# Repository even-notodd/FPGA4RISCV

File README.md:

# FPGA4RISCV
This project is an attempt to build hardware (SOM and baseboard) capable of runnig Linux on RISCV MCU implemented in FPGA.
## This is work in progress, not finished project (!).
Overview: 

[Edit this diagram](https://app.diagrams.net/?url=https://raw.githubusercontent.com/even-notodd/FPGA4RISCV/DOCs/architecture.drawio)

# SOM
SOM is supposed to be designed in a format of a SO-DIMM card (Small Outline Dual Inline Memory Module) with standard 200 pin board edge connector.
SoM is based on Lattice FPGA chip LFE5UM5G-85F with dedicated DDR3 memory.

# Baseboard
Baseboard is supposed to be more or less generic baseboard and planned to be used with other SoMs. Concequently it must have:
- Power supply with several standard voltages
- Ethernet Phy
- USB 2.0 Phy & USB Hub
- USB 3.0
- PCIe
- USB-JTAG
- USB-UART
- GPIO headers
- UART/I2C/SPI headers
- HDMI

## License
See the  for details.

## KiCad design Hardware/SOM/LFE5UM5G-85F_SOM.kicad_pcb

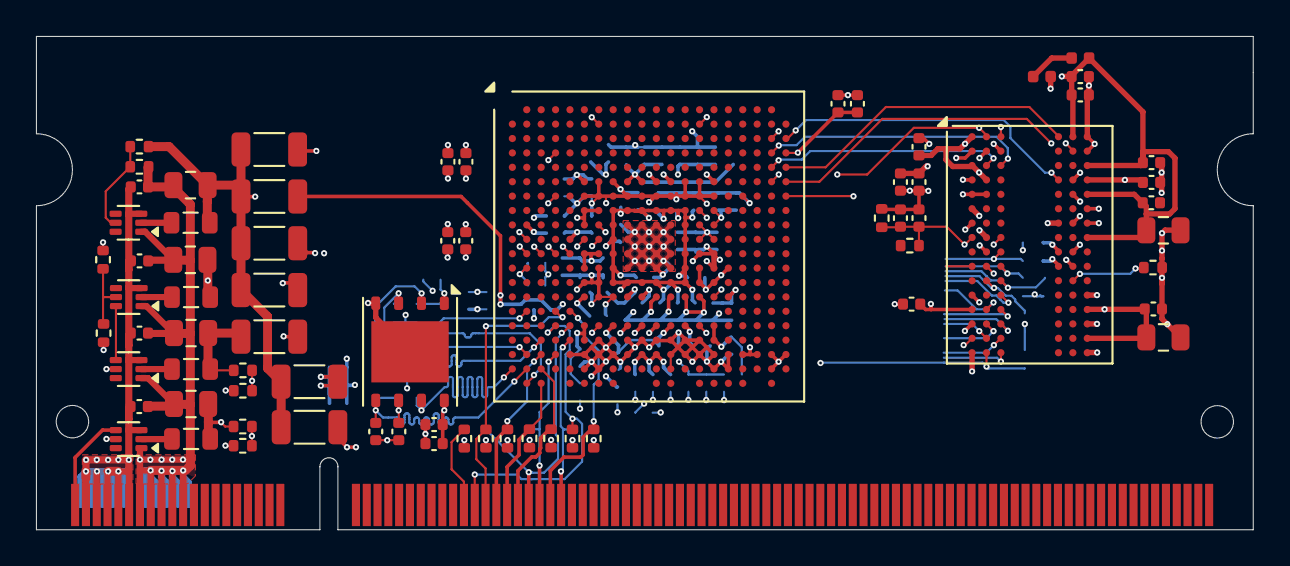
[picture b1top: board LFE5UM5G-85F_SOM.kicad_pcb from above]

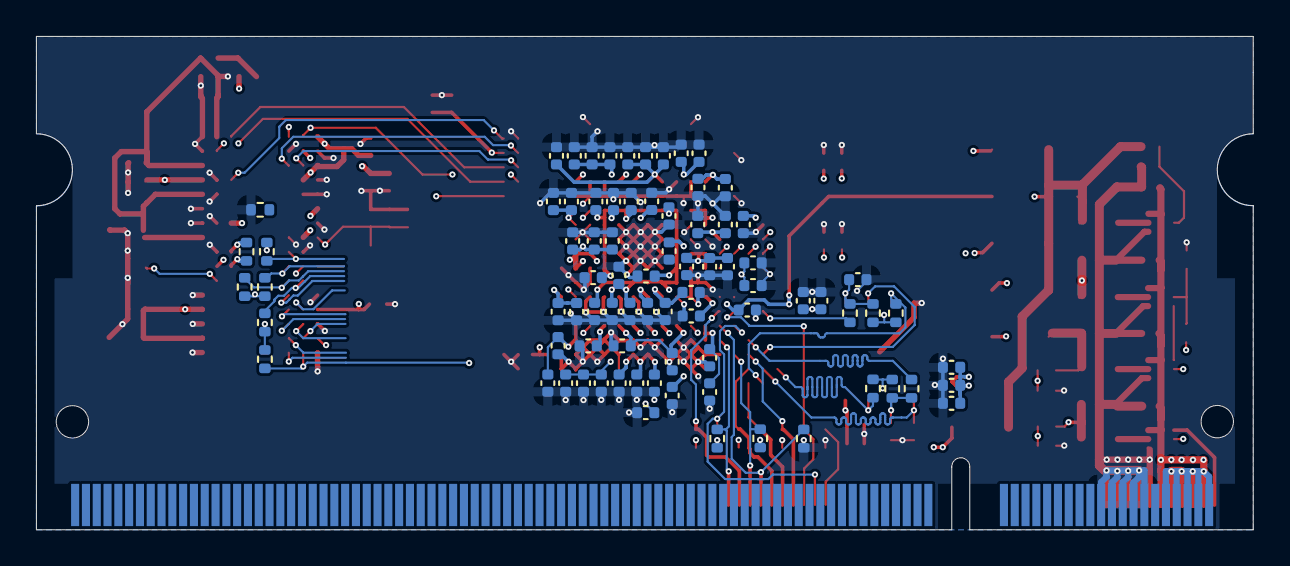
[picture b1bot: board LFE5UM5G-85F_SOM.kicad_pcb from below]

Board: 8 copper layers, 67.6 x 27.4 mm, 151 parts (80 on the bottom side), 94 nets.

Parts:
C1, C2, C3, C4, C5, C6, C7, C8, C9, C13, C14, C15, C17, C18, C19, C21, C22, C23, C27, C28, C30, C31, C32, C34, C46, C47, C48, C49, C50, C51, C52, C53, C54, C64, C65, C66, C67, C68, C69, C71, C73, C75, C76, C77, C84, C85, C86, C87, C89, C93: 100nF; C_0402_1005Metric
C10, C11, C12, C24, C26, C35, C36, C38, C39, C40, C41, C42, C56, C57, C58, C59, C63, C94, C95, C96, C99, C100: 10uF; C_0402_1005Metric
C43, C44, C45, C55, C60, C61, C62, C70, C72, C74, C80, C81, C82, C83, C88: 1uF; C_0402_1005Metric
C78, C79, C97, C98, C101, C102: 22uF; C_0805_2012Metric
C90, C91, C92: 22pF; C_0402_1005Metric
FB1, FB2, FB3, FB4, FB5, FB6, FB7: FerriteBead; L_1206_3216Metric
FB8, FB9: FerriteBead; L_0402_1005Metric
J1: SODIMM-200_Split; SODIMM-200_1.8V_Card_edge
L1, L2, L3, L4: 1uH; L_0805_2012Metric
R1: 100R; R_0402_1005Metric
R2, R3, R4, R5, R6, R7, R25, R26, R27, R28, R29, R30: 10K; R_0402_1005Metric
R8: 240R; R_0402_1005Metric
R9, R10: 1K; R_0402_1005Metric
R11: 49.9R; R_0402_1005Metric
R12, R14, R16: 4k7; R_0402_1005Metric
R13: 0R; R_0402_1005Metric
R15: 1k; R_0402_1005Metric
R17: 442k; R_0402_1005Metric
R18, R20, R22, R23, R24: 100K; R_0402_1005Metric
R19: 316k; R_0402_1005Metric
R21: 150k; R_0402_1005Metric
R31, R32, R33, R34: 4.7k; R_0402_1005Metric
U1: LFE5UM5G-85F; Lattice_caBGA-381_17x17mm_Layout20x20_P0.8mm
U2: AS4C256M16D3; BGA-96_9.0x13.0mm_Layout2x3x16_P0.8mm
U3: W25Q128JVP; WSON-8-1EP_6x5mm_P1.27mm_EP3.4x4.3mm
U4, U5, U6, U7: TPS62A02ADRL; SOT-563

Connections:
1.2V: C1.2, C5.2, C9.2, C13.2, C14.2, C18.2, C22.2, C23.2, C27.2, C31.2, C35.2, C39.2, C102.2, FB1.1, FB2.1, FB3.1, FB5.1, FB6.1, FB7.1, L4.2, R23.2, U1.H8 (VCC), U1.H9 (VCC), U1.H10 (VCC), U1.H11 (VCC), U1.H12 (VCC), U1.H13 (VCC), U1.J8 (VCC), U1.J13 (VCC), U1.K8 (VCC), U1.K13 (VCC), U1.L8 (VCC), U1.L13 (VCC), U1.M8 (VCC), U1.M13 (VCC), U1.N8 (VCC), U1.N9 (VCC), U1.N10 (VCC), U1.N11 (VCC), U1.N12 (VCC), U1.N13 (VCC)
1.5V: C2.2, C3.2, C4.2, C6.2, C7.2, C8.2, C10.2, C11.2, C12.2, C28.2, C32.2, C36.2, C101.2, FB8.1, FB9.1, L3.2, R9.2, R21.2, U1.F9 (VCCIO0), U1.F10 (VCCIO0), U1.H14 (VCCIO2), U1.H15 (VCCIO2), U1.J15 (VCCIO2), U1.L6 (VCCIO6), U1.L7 (VCCIO6), U1.L14 (VCCIO3), U1.L15 (VCCIO3), U1.M6 (VCCIO6), U1.M15 (VCCIO3)
2.5V: C98.2, FB4.1, L2.2, R19.2
2.5V_A: C46.2, C50.2, C54.2, C55.2, C59.2, C63.2, FB4.2, U1.F6 (VCCAUX), U1.F15 (VCCAUX), U1.P6 (VCCAUX), U1.P15 (VCCAUX), U1.V10 (VCCAUXA0), U1.V11 (VCCAUXA0), U1.V17 (VCCAUXA1), U1.V18 (VCCAUXA1)
3.3V: C15.2, C17.2, C19.2, C21.2, C24.2, C26.2, C30.2, C34.2, C38.2, C93.2, C94.2, C97.2, L1.2, R12.1, R14.1, R15.1, R16.1, R17.2, R25.1, R26.1, R27.1, R28.1, R31.2, R32.2, R33.2, U1.F11 (VCCIO1), U1.F12 (VCCIO1), U1.H6 (VCCIO7), U1.H7 (VCCIO7), U1.J6 (VCCIO7), U1.P9 (VCCIO8), U1.P10 (VCCIO8), U3.8 (VCC)
5V: C95.2, C96.2, C99.2, C100.2, J1.2, J1.3, J1.4, J1.5, J1.6, J1.7, J1.8, J1.9, J1.10, J1.11, U4.3 (VIN), U5.3 (VIN), U6.3 (VIN), U7.3 (VIN)
/DDR/ZQ: R8.1, U2.L8 (ZQ)
/Power Supply/1.5V_PG: U5.4 (EN), U6.6 (PG), U7.4 (EN)
BB_PGOOD: J1.1, U4.4 (EN), U6.4 (EN)
BOOT_MODE_0: J1.61, R30.2, U1.U4 (CFG_0)
BOOT_MODE_1: J1.63, R28.2, U1.T4 (CFG_1)
BOOT_MODE_2: J1.65, R29.2, U1.R4 (CFG_2)
DDR_A0: U1.L20 (PR47A), U2.N3 (A0)
DDR_A1: U1.M20 (PR47B), U2.P7 (A1)
DDR_A2: U1.L19 (PR47C), U2.P3 (A2)
DDR_A3: U1.M19 (PR47D), U2.N2 (A3)
DDR_A4: U1.L16 (PR50A), U2.P8 (A4)
DDR_A5: U1.L17 (PR50B), U2.P2 (A5)
DDR_A6: U1.L18 (PR50C), U2.R8 (A6)
DDR_A7: U1.M18 (PR50D), U2.R2 (A7)
DDR_A8: U1.N18 (PR53C), U2.T8 (A8)
DDR_A9: U1.P17 (PR53D), U2.R3 (A9)
DDR_A10: U1.C18 (PR11A), U2.L7 (A10/AP)
DDR_A11: U1.D17 (PR11B), U2.R7 (A11)
DDR_A12: U1.E16 (PR11C), U2.N7 (A12/~BC)
DDR_A13: U1.F16 (PR11D), U2.T3 (A13)
DDR_A14: U1.D18 (PR14A), U2.T7 (A14)
DDR_BA0: U1.E17 (PR14B), U2.M2 (BA0)
DDR_BA1: U1.E18 (PR14C), U2.N8 (BA1)
DDR_BA2: U1.F18 (PR14D), U2.M3 (BA2)
DDR_CAS: R6.1, U1.J17 (PR20C), U2.K3 (~CAS)
DDR_CKE: U1.G16 (PR17C), U2.K9 (CKE)
DDR_CK_N: R1.2, U1.G18 (PR17B), U2.K7 (~CK)
DDR_CK_P: R1.1, U1.F17 (PR17A), U2.J7 (CK)
DDR_CS: R4.1, U1.H18 (PR20A), U2.L2 (~CS)
DDR_DQ0: U1.N19 (PR83A), U2.E3 (DQ0)
DDR_DQ1: U1.N20 (PR83B), U2.F7 (DQ1)
DDR_DQ2: U1.P19 (PR83C), U2.F2 (DQ2)
DDR_DQ3: U1.P18 (PR83D), U2.F8 (DQ3)
DDR_DQ4: U1.P20 (PR86A), U2.H3 (DQ4)
DDR_DQ5: U1.R20 (PR86B), U2.H8 (DQ5)
DDR_DQ6: U1.T20 (PR86C), U2.G2 (DQ6)
DDR_DQ7: U1.U20 (PR86D), U2.H7 (DQ7)
DDR_DQ8: U1.C20 (PR35A), U2.D7 (DQ8)
DDR_DQ9: U1.D19 (PR35B), U2.C3 (DQ9)
DDR_DQ10: U1.K18 (PR41D), U2.C8 (DQ10)
DDR_DQ11: U1.E19 (PR35D), U2.C2 (DQ11)
DDR_DQ12: U1.E20 (PR38A), U2.A7 (DQ12)
DDR_DQ13: U1.F19 (PR38B), U2.A2 (DQ13)
DDR_DQ14: U1.F20 (PR38C), U2.B8 (DQ14)
DDR_DQ15: U1.G20 (PR38D), U2.A3 (DQ15)
DDR_LDM: U1.U19 (PR89C), U2.E7 (LDM)
DDR_LDQS_N: U1.R18 (PR89B), U2.G3 (~LDQS)
DDR_LDQS_P: U1.T19 (PR89A), U2.F3 (LDQS)
DDR_ODT: R2.1, U1.K16 (PR29A), U2.K1 (ODT)
DDR_RAS: R5.1, U1.H17 (PR20B), U2.J3 (~RAS)
DDR_RST: R3.1, U1.H16 (PR17D), U2.T2 (~RESET)
DDR_UDM: U1.J18 (PR41C), U2.D3 (UDM)
DDR_UDQS_N: U1.H20 (PR41B), U2.B7 (~UDQS)
DDR_UDQS_P: U1.G19 (PR41A), U2.C7 (UDQS)
DDR_VDDQ_1.5V: C76.2, C78.2, C80.2, C82.2, C84.2, C86.2, FB8.2, U2.A1 (VDDQ), U2.A8 (VDDQ), U2.C1 (VDDQ), U2.C9 (VDDQ), U2.D2 (VDDQ), U2.E9 (VDDQ), U2.F1 (VDDQ), U2.H2 (VDDQ), U2.H9 (VDDQ)
DDR_VDD_1.5V: C77.2, C79.2, C81.2, C83.2, C85.2, C87.2, FB9.2, R3.2, R4.2, R5.2, R6.2, R7.2, U2.B2 (VDD), U2.D9 (VDD), U2.G7 (VDD), U2.K2 (VDD), U2.K8 (VDD), U2.N1 (VDD), U2.N9 (VDD), U2.R1 (VDD), U2.R9 (VDD)
DDR_VREF: C70.2, C71.2, C72.2, C73.2, C74.2, C75.2, C88.2, C89.2, R9.1, R10.2, U1.D20 (PR35C), U1.K5 (PL56B), U1.P16 (PR56B), U2.H1 (VREFDQ), U2.M8 (VREFCA)
DDR_WE: R7.1, U1.J16 (PR20D), U2.L3 (~WE)
DONE: J1.69, R27.2, U1.Y3 (DONE)
GND: C1.1, C2.1, C3.1, C4.1, C5.1, C6.1, C7.1, C8.1, C9.1, C10.1, C11.1, C12.1, C13.1, C14.1, C15.1, C17.1, C18.1, C19.1, C21.1, C22.1, C23.1, C24.1, C26.1, C27.1, C28.1, C30.1, C31.1, C32.1, C34.1, C35.1, C36.1, C38.1, C39.1, C40.1, C41.1, C42.1, C43.1, C44.1, C45.1, C46.1, C47.1, C48.1, C49.1, C50.1, C51.1, C52.1, C53.1, C54.1, C55.1, C56.1, C57.1, C58.1, C59.1, C60.1, C61.1, C62.1, C63.1, C64.1, C65.1, C66.1, C67.1, C68.1, C69.1, C70.1, C71.1, C72.1, C73.1, C74.1, C75.1, C76.1, C77.1, C78.1, C79.1, C80.1, C81.1, C82.1, C83.1, C84.1, C85.1, C86.1, C87.1, C88.1, C89.1, C90.2, C91.2, C92.2, C93.1, C94.1, C95.1, C96.1, C97.1, C98.1, C99.1, C100.1, C101.1, C102.1, J1.13, J1.14, J1.15, J1.16, J1.17, J1.18, J1.19, J1.20, J1.21, J1.22, R2.2, R8.2, R10.1, R18.1, R20.1, R22.1, R24.1, R29.1, R30.1, R34.2, U1.B7 (GND), U1.B14 (GND), U1.C19 (GND), U1.D4 (GND), U1.F7 (GND), U1.F8 (GND), U1.F13 (GND), U1.F14 (GND), U1.G4 (GND), U1.G6 (GND), U1.G7 (GND), U1.G8 (GND), U1.G9 (GND), U1.G10 (GND), U1.G11 (GND), U1.G12 (GND), U1.G13 (GND), U1.G14 (GND), U1.G15 (GND), U1.G17 (GND), U1.H19 (GND), U1.J2 (GND), U1.J7 (GND), U1.J9 (GND), U1.J10 (GND), U1.J11 (GND), U1.J12 (GND), U1.J14 (GND), U1.K6 (GND), U1.K7 (GND), U1.K9 (GND), U1.K10 (GND), U1.K11 (GND), U1.K12 (GND), U1.K14 (GND), U1.K15 (GND), U1.L9 (GND), U1.L10 (GND), U1.L11 (GND), U1.L12 (GND), U1.M2 (GND), U1.M7 (GND), U1.M9 (GND), U1.M10 (GND), U1.M11 (GND), U1.M12 (GND), U1.M14 (GND), U1.M16 (GND), U1.N6 (GND), U1.N7 (GND), U1.N14 (GND), U1.N15 (GND), U1.P7 (GND), U1.P8 (GND), U1.P11 (GND), U1.P12 (GND), U1.P13 (GND), U1.P14 (GND), U1.R19 (GND), U1.U7 (GND), U1.U8 (GND), U1.U9 (GND), U1.U10 (GND), U1.U11 (GND), U1.U12 (GND), U1.U13 (GND), U1.U14 (GND), U1.V5 (GND), U1.V6 (GND), U1.V7 (GND), U1.V8 (GND), U1.V9 (GND), U1.V12 (GND), U1.V13 (GND), U1.V14 (GND), U1.V15 (GND), U1.V16 (GND), U1.V19 (GND), U1.V20 (GND), U1.W6 (GND), U1.W7 (GND), U1.W12 (GND), U1.W15 (GND), U1.W16 (GND), U1.W19 (GND), U2.A9 (VSS), U2.B1 (VSSQ), U2.B3 (VSS), U2.B9 (VSSQ), U2.D1 (VSSQ), U2.D8 (VSSQ), U2.E1 (VSS), U2.E2 (VSSQ), U2.E8 (VSSQ), U2.F9 (VSSQ), U2.G1 (VSSQ), U2.G8 (VSS), U2.G9 (VSSQ), U2.J2 (VSS), U2.J8 (VSS), U2.M1 (VSS), U2.M9 (VSS), U2.P1 (VSS), U2.P9 (VSS), U2.T1 (VSS), U2.T9 (VSS), U3.4 (GND), U3.9 (EP), U4.1 (GND), U5.1 (GND), U6.1 (GND), U7.1 (GND)
INIT#: J1.67, R26.2, U1.V3 (~INIT)
JTAG_TCK: J1.73, R34.1, U1.T5 (TCK)
JTAG_TDI: J1.77, R32.1, U1.R5 (TDI)
JTAG_TDO: J1.75, R31.1, U1.V4 (TDO)
JTAG_TMS: J1.79, R33.1, U1.U5 (TMS)
unnamed: C91.1, R11.1, R15.2, U3.6 (CLK)
unnamed: C90.1, R13.1, R16.2, U3.1 (~CS)
unnamed: R17.1, R18.2, U4.5 (FB)
unnamed: L1.1, U4.2 (SW)
unnamed: R19.1, R20.2, U5.5 (FB)
unnamed: L2.1, U5.2 (SW)
unnamed: R21.1, R22.2, U6.5 (FB)
unnamed: L3.1, U6.2 (SW)
unnamed: R23.1, R24.2, U7.5 (FB)
unnamed: L4.1, U7.2 (SW)
PROGRAM#: J1.71, R25.2, U1.W3 (~PROGRAM)
QSPI_CLK: R11.2, U1.U3 (CCLK)
QSPI_CS: R13.2, U1.R2 (PB15A)
QSPI_MISO/DQ1: U1.V2 (PB11A), U3.2 (DO/IO_{1})
QSPI_MOSI/DQ0: C92.1, U1.W2 (PB11B), U3.5 (DI/IO_{0})
QSPI_RST/DQ3: R12.2, U1.W1 (PB9A), U3.7 (~HOLD/~RESET/IO_{3})
QSPI_WP/DQ2: R14.2, U1.Y2 (PB9B), U3.3 (~WP/IO_{2})
VCCA0: C40.2, C43.2, C47.2, C51.2, FB1.2, U1.T6 (VCCA0), U1.U6 (VCCA0)
VCCA1: C56.2, C60.2, C64.2, C67.2, FB5.2, U1.T15 (VCCA1), U1.U15 (VCCA1)
VCCHTX0: C41.2, C44.2, C48.2, C52.2, FB2.2, U1.T7 (VCCHTX0_D0CH0), U1.T11 (VCCHTX0_D1CH0)
VCCHTX1: C57.2, C61.2, C65.2, C68.2, FB6.2, U1.T10 (VCCHTX1_D0CH1), U1.T14 (VCCHTX1_D1CH1)
VCC_SER_0: C42.2, C45.2, C49.2, C53.2, FB3.2, U1.T8 (VCCHRX0_D0CH0), U1.T12 (VCCHRX0_D1CH0)
VCC_SER_1: C58.2, C62.2, C66.2, C69.2, FB7.2, U1.T9 (VCCHRX1_D0CH1), U1.T13 (VCCHRX1_D1CH1)

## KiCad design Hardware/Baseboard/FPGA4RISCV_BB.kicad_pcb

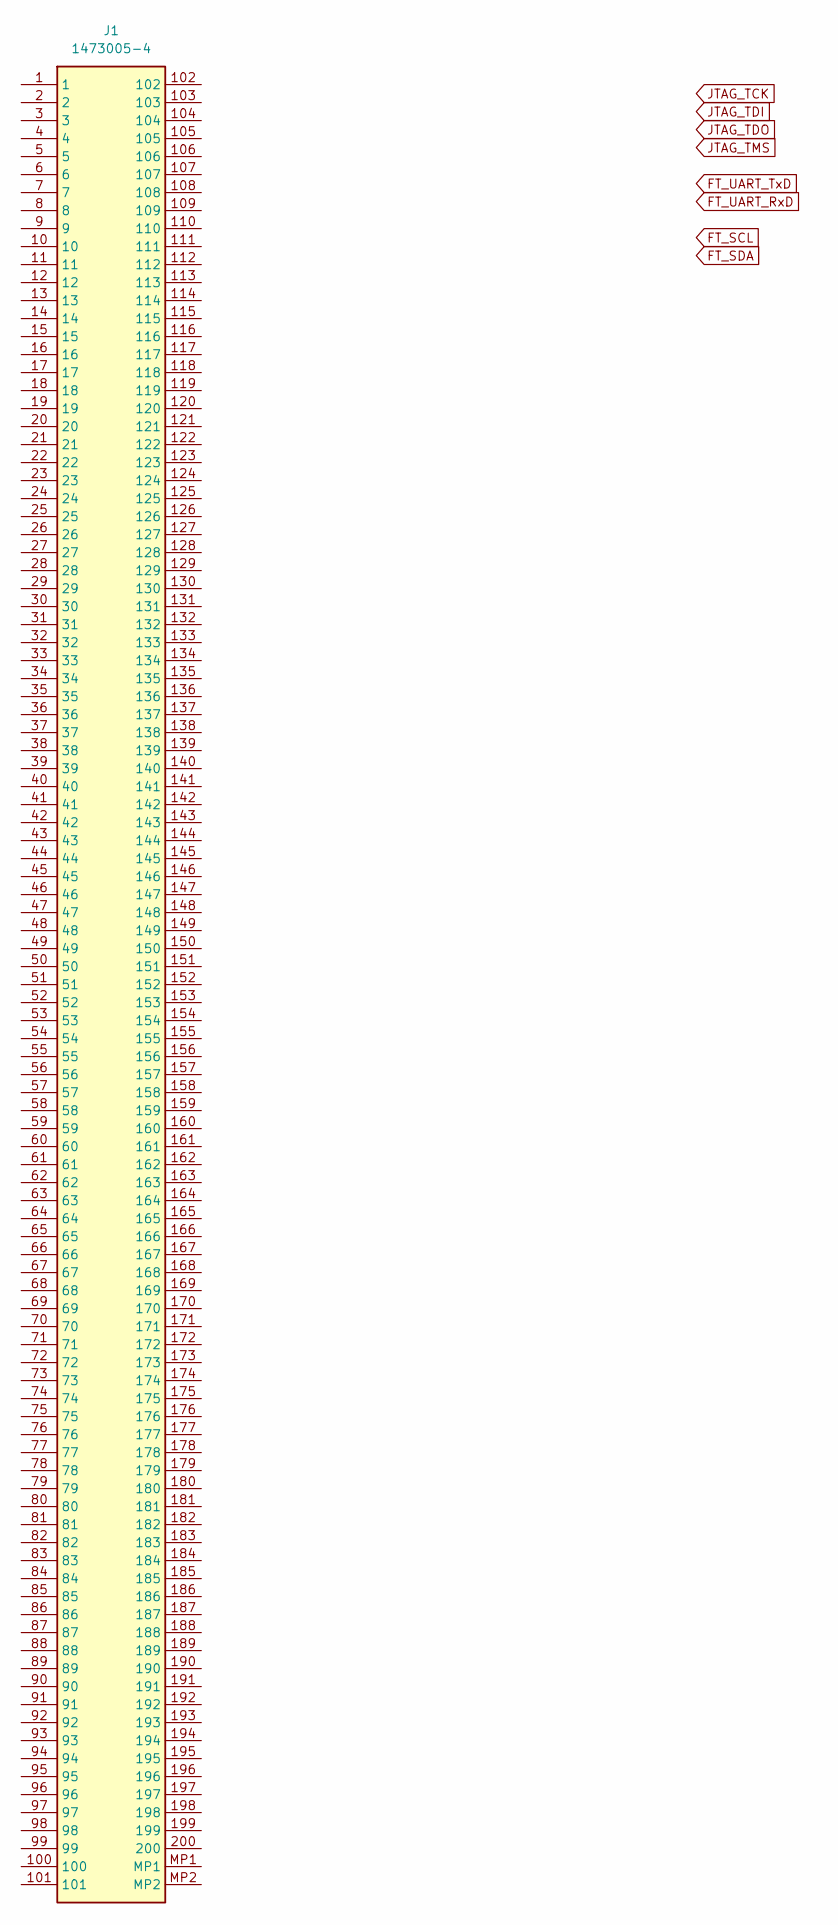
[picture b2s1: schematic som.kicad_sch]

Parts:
J1: 1473005-4; 14730054; Mouser Part Number 571-1473005-4

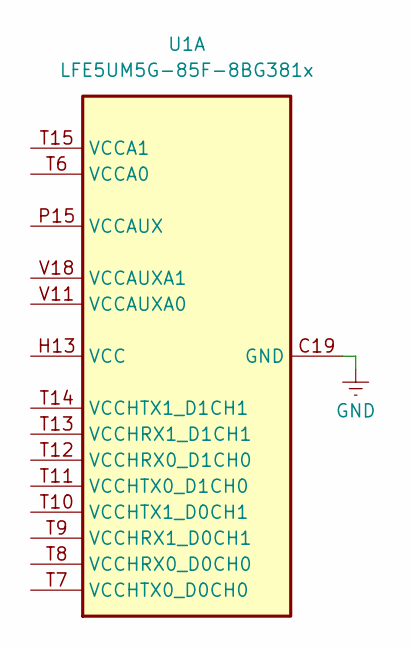
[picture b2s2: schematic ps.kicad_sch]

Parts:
U1: LFE5UM5G-85F-8BG381x; Lattice_caBGA-381_17.0x17.0mm_Layout20x20_P0.8mm_Ball0.4mm_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

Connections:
unnamed: U1.B7 (GND), U1.B14 (GND), U1.C19 (GND), U1.D4 (GND), U1.F7 (GND), U1.F8 (GND), U1.F13 (GND), U1.F14 (GND), U1.G4 (GND), U1.G6 (GND), U1.G7 (GND), U1.G8 (GND), U1.G9 (GND), U1.G10 (GND), U1.G11 (GND), U1.G12 (GND), U1.G13 (GND), U1.G14 (GND), U1.G15 (GND), U1.G17 (GND), U1.H19 (GND), U1.J2 (GND), U1.J7 (GND), U1.J9 (GND), U1.J10 (GND), U1.J11 (GND), U1.J12 (GND), U1.J14 (GND), U1.K6 (GND), U1.K7 (GND), U1.K9 (GND), U1.K10 (GND), U1.K11 (GND), U1.K12 (GND), U1.K14 (GND), U1.K15 (GND), U1.L9 (GND), U1.L10 (GND), U1.L11 (GND), U1.L12 (GND), U1.M2 (GND), U1.M7 (GND), U1.M9 (GND), U1.M10 (GND), U1.M11 (GND), U1.M12 (GND), U1.M14 (GND), U1.M16 (GND), U1.N6 (GND), U1.N7 (GND), U1.N14 (GND), U1.N15 (GND), U1.P7 (GND), U1.P8 (GND), U1.P11 (GND), U1.P12 (GND), U1.P13 (GND), U1.P14 (GND), U1.R19 (GND), U1.U7 (GND), U1.U8 (GND), U1.U9 (GND), U1.U10 (GND), U1.U11 (GND), U1.U12 (GND), U1.U13 (GND), U1.U14 (GND), U1.V5 (GND), U1.V6 (GND), U1.V7 (GND), U1.V8 (GND), U1.V9 (GND), U1.V12 (GND), U1.V13 (GND), U1.V14 (GND), U1.V15 (GND), U1.V16 (GND), U1.V19 (GND), U1.V20 (GND), U1.W6 (GND), U1.W7 (GND), U1.W12 (GND), U1.W15 (GND), U1.W16 (GND), U1.W19 (GND)
unnamed: U1.F6 (VCCAUX), U1.F15 (VCCAUX), U1.P6 (VCCAUX), U1.P15 (VCCAUX)
unnamed: U1.H8 (VCC), U1.H9 (VCC), U1.H10 (VCC), U1.H11 (VCC), U1.H12 (VCC), U1.H13 (VCC), U1.J8 (VCC), U1.J13 (VCC), U1.K8 (VCC), U1.K13 (VCC), U1.L8 (VCC), U1.L13 (VCC), U1.M8 (VCC), U1.M13 (VCC), U1.N8 (VCC), U1.N9 (VCC), U1.N10 (VCC), U1.N11 (VCC), U1.N12 (VCC), U1.N13 (VCC)
unnamed: U1.T6 (VCCA0), U1.U6 (VCCA0)
unnamed: U1.T15 (VCCA1), U1.U15 (VCCA1)
unnamed: U1.V10 (VCCAUXA0), U1.V11 (VCCAUXA0)
unnamed: U1.V17 (VCCAUXA1), U1.V18 (VCCAUXA1)

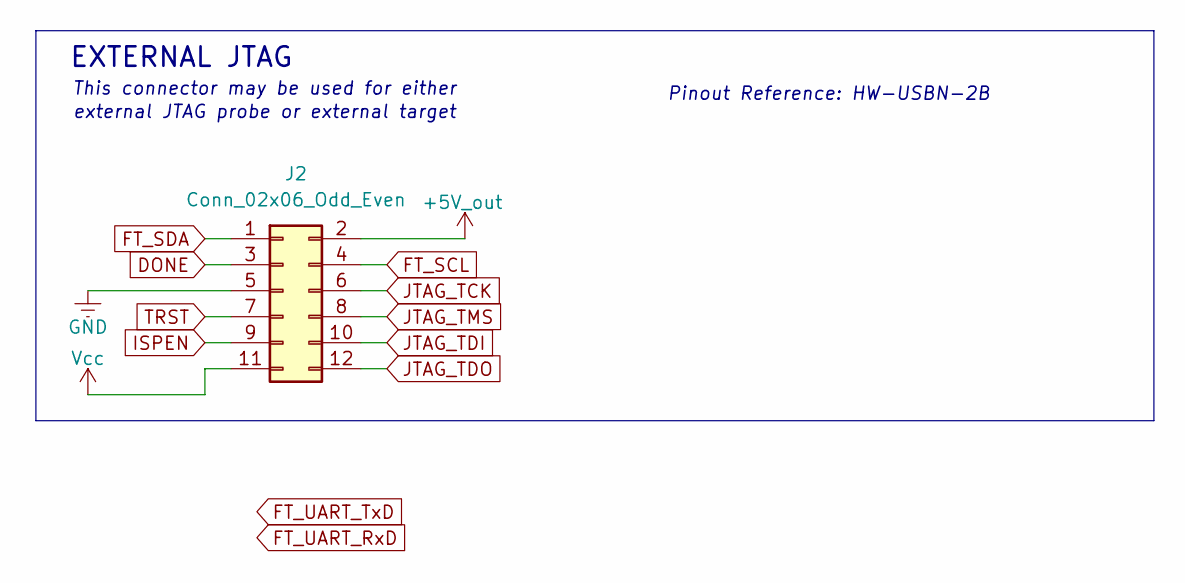
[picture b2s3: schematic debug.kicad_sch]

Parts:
J2: Conn_02x06_Odd_Even; PinHeader_2x06_P2.54mm_Vertical

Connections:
+5V_out: J2.2
DONE: J2.3
FT_SCL: J2.4; also elsewhere on the board
FT_SDA: J2.1; also elsewhere on the board
GND: J2.5; also elsewhere on the board
ISPEN: J2.9
JTAG_TCK: J2.6; also elsewhere on the board
JTAG_TDI: J2.10; also elsewhere on the board
JTAG_TDO: J2.12; also elsewhere on the board
JTAG_TMS: J2.8; also elsewhere on the board
TRST: J2.7
Vcc: J2.11

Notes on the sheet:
external JTAG probe or external target
Pinout Reference: HW-USBN-2B
EXTERNAL JTAG
This connector may be used for either

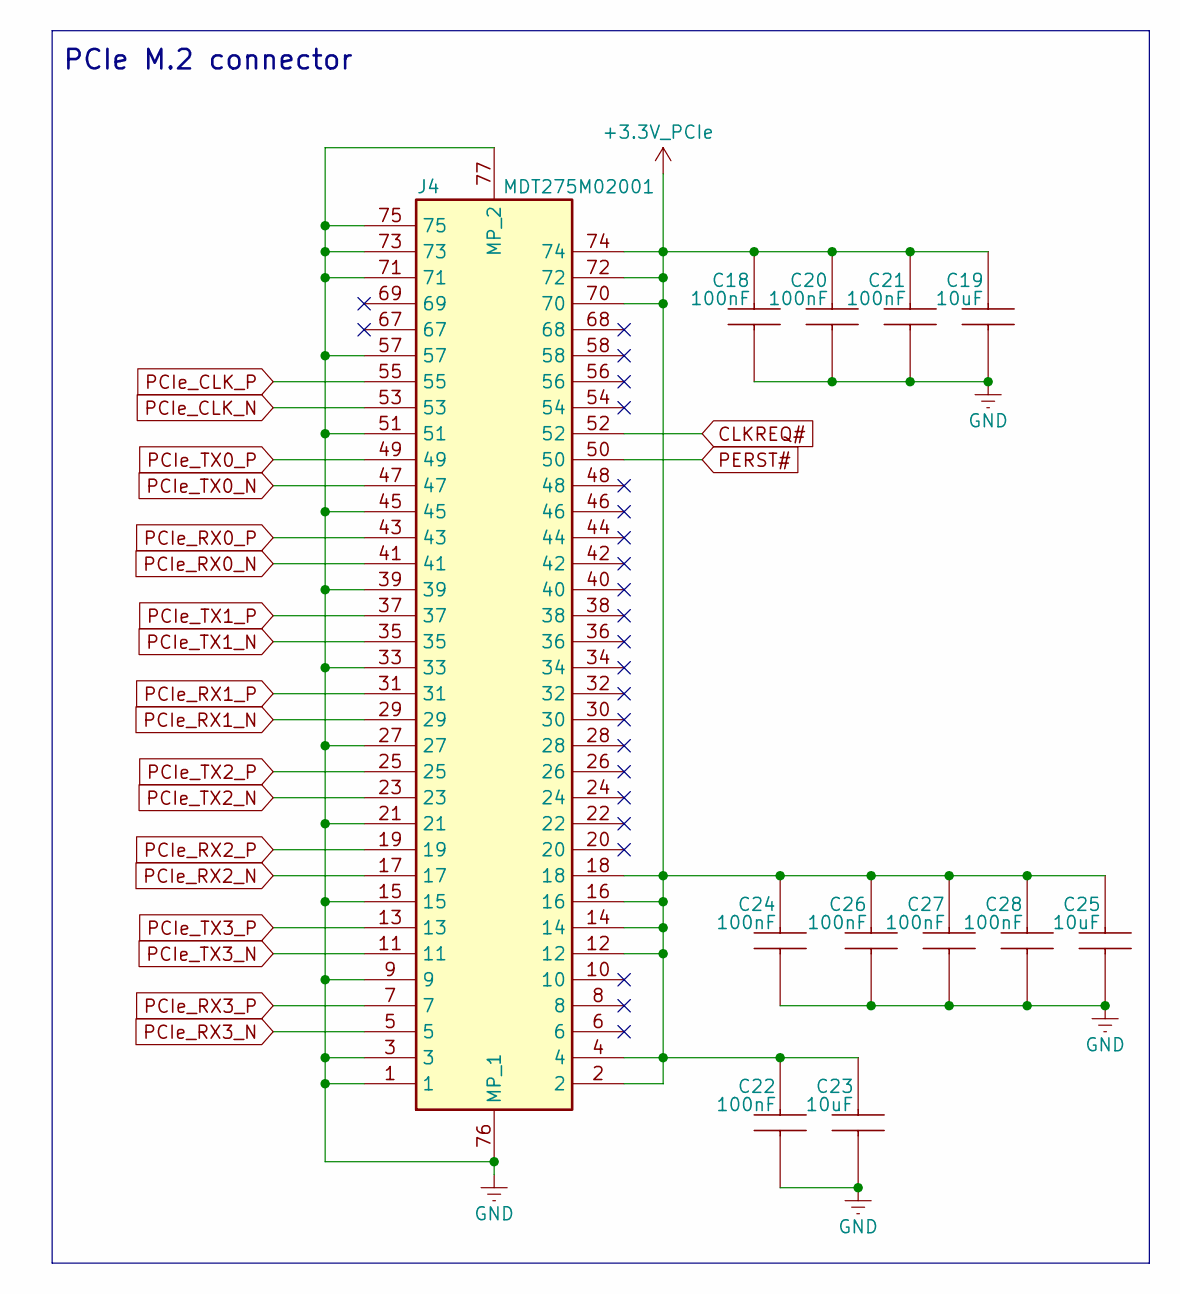
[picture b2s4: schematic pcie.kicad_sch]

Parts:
C18, C20, C21, C22, C24, C26, C27, C28: 100nF; C_0402_1005Metric; MPN 885012205092
C19, C23, C25: 10uF; C_0402_1005Metric; MPN 885012105020
J4: MDT275M02001; Mouser Part Number 523-MDT275M02001

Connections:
+3.3V_PCIe: C18.2, C19.2, C20.2, C21.2, C22.2, C23.2, C24.2, C25.2, C26.2, C27.2, C28.2, J4.2, J4.4, J4.12, J4.14, J4.16, J4.18, J4.70, J4.72, J4.74
CLKREQ#: J4.52
GND: C18.1, C19.1, C20.1, C21.1, C22.1, C23.1, C24.1, C25.1, C26.1, C27.1, C28.1, J4.1, J4.3, J4.9, J4.15, J4.21, J4.27, J4.33, J4.39, J4.45, J4.51, J4.57, J4.71, J4.73, J4.75, J4.76 (MP_1), J4.77 (MP_2); also elsewhere on the board
PCIe_CLK_N: J4.53
PCIe_CLK_P: J4.55
PCIe_RX0_N: J4.41
PCIe_RX0_P: J4.43
PCIe_RX1_N: J4.29
PCIe_RX1_P: J4.31
PCIe_RX2_N: J4.17
PCIe_RX2_P: J4.19
PCIe_RX3_N: J4.5
PCIe_RX3_P: J4.7
PCIe_TX0_N: J4.47
PCIe_TX0_P: J4.49
PCIe_TX1_N: J4.35
PCIe_TX1_P: J4.37
PCIe_TX2_N: J4.23
PCIe_TX2_P: J4.25
PCIe_TX3_N: J4.11
PCIe_TX3_P: J4.13
PERST#: J4.50

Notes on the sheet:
PCIe M.2 connector

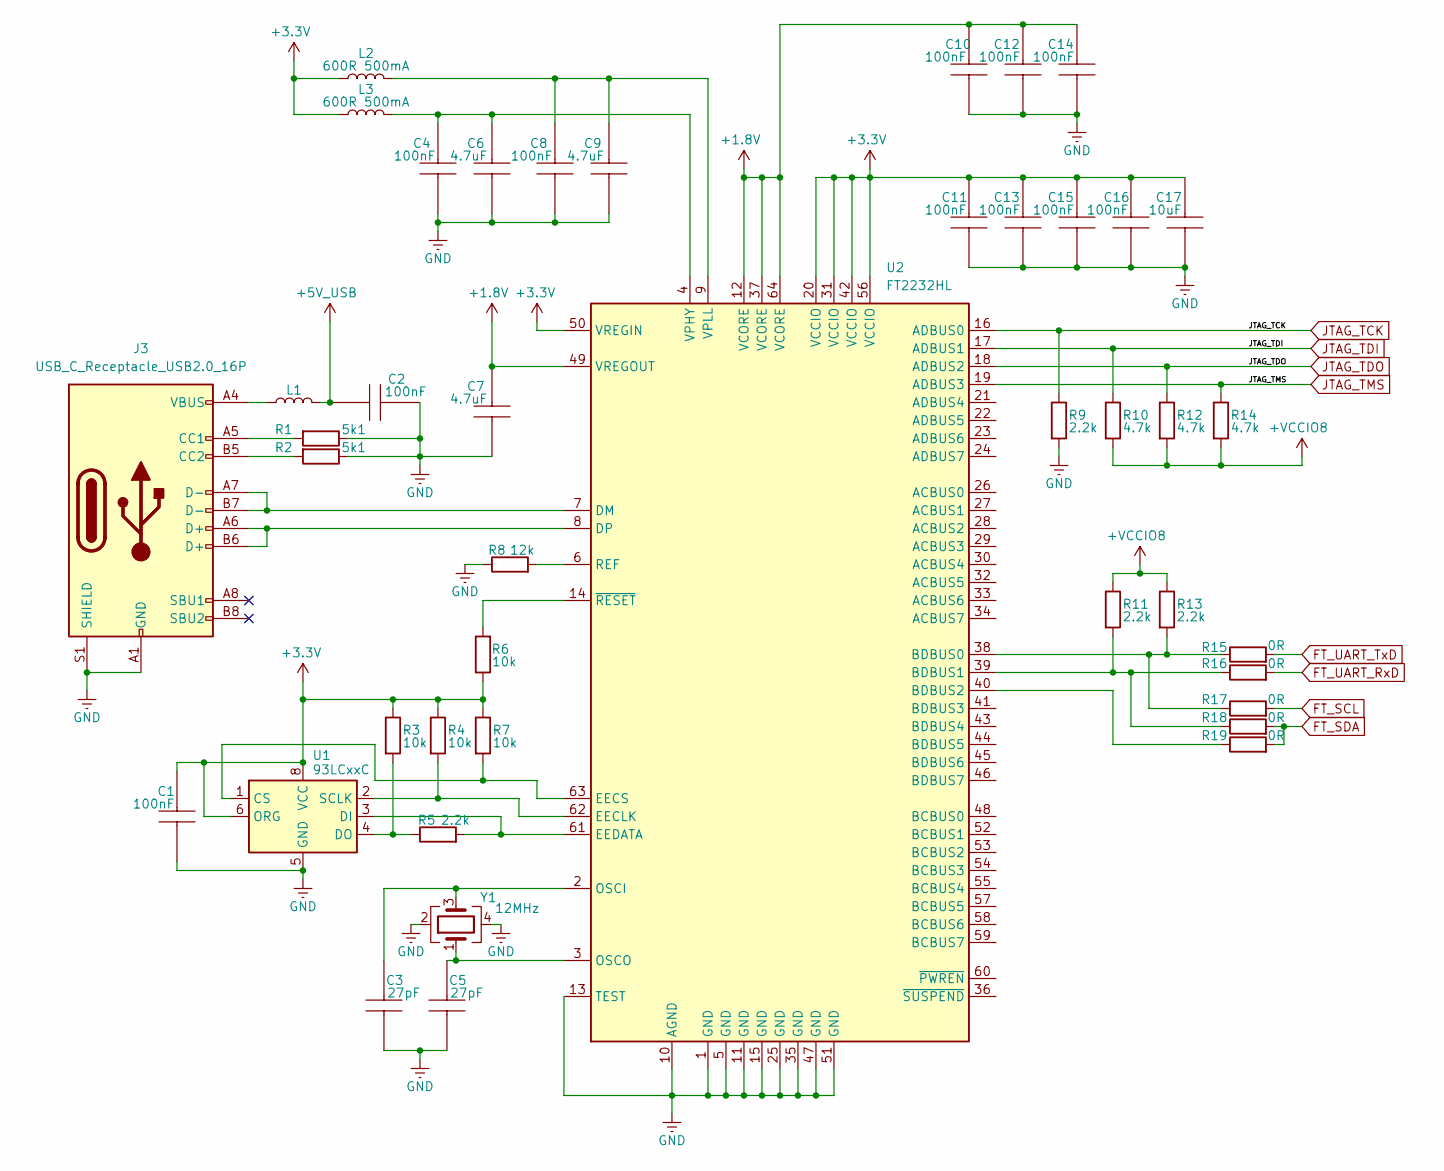
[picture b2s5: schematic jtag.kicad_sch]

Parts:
C1, C2, C4, C8, C10, C11, C12, C13, C14, C15, C16: 100nF; C_0402_1005Metric; MPN 885012205092
C3, C5: 27pF; C_0402_1005Metric; MPN 885392005116
C6, C7, C9: 4.7uF; C_0402_1005Metric; MPN 885012105008
C17: 10uF; C_0402_1005Metric; MPN 885012105020
J3: USB_C_Receptacle_USB2.0_16P; USB_C_Receptacle_GCT_USB4110; MPN USB4110-GF-A
L1, L2, L3: 600R 500mA; MPN 560112110245
R1, R2: 5k1; R_0402_1005Metric; MPN 560112120019
R3, R4, R6, R7: 10k; R_0402_1005Metric; MPN 560112110020
R5, R9, R11, R13: 2.2k; R_0402_1005Metric; MPN 560112110087
R8: 12k; R_0402_1005Metric; MPN 560112116040
R10, R12, R14: 4.7k; R_0402_1005Metric; MPN 560112110245
R15, R16, R17, R18, R19: 0R; R_0402_1005Metric; MPN 560112110087
U1: 93LCxxC
U2: FT2232HL; LQFP-64_10x10mm_P0.5mm
Y1: 12MHz; Crystal_SMD_3225-4Pin_3.2x2.5mm; MPN ABM8-12.000MHZ-D4H-T

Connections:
+1.8V: C7.2, C10.2, C12.2, C14.2, U2.12 (VCORE), U2.37 (VCORE), U2.49 (VREGOUT), U2.64 (VCORE)
+3.3V: C1.2, C11.2, C13.2, C15.2, C16.2, C17.2, L2.1, L3.1, R3.1, R4.1, R6.1, R7.1, U1.6 (ORG), U1.8 (VCC), U2.20 (VCCIO), U2.31 (VCCIO), U2.42 (VCCIO), U2.50 (VREGIN), U2.56 (VCCIO)
+5V_USB: C2.1, L1.2
+VCCIO8: R10.2, R11.1, R12.2, R13.1, R14.2
FT_SCL: R17.2; also elsewhere on the board
FT_SDA: R18.2, R19.2; also elsewhere on the board
FT_UART_RxD: R16.2
FT_UART_TxD: R15.2
GND: C1.1, C2.2, C3.1, C4.1, C5.1, C6.1, C7.1, C8.1, C9.1, C10.1, C11.1, C12.1, C13.1, C14.1, C15.1, C16.1, C17.1, J3.A1 (GND), J3.A12 (GND), J3.B1 (GND), J3.B12 (GND), J3.S1 (SHIELD), R1.1, R2.1, R8.1, R9.2, U1.5 (GND), U2.1 (GND), U2.5 (GND), U2.10 (AGND), U2.11 (GND), U2.13 (TEST), U2.15 (GND), U2.25 (GND), U2.35 (GND), U2.47 (GND), U2.51 (GND), Y1.2, Y1.4; also elsewhere on the board
JTAG_TCK: R9.1, U2.16 (ADBUS0); also elsewhere on the board
JTAG_TDI: R10.1, U2.17 (ADBUS1); also elsewhere on the board
JTAG_TDO: R12.1, U2.18 (ADBUS2); also elsewhere on the board
JTAG_TMS: R14.1, U2.19 (ADBUS3); also elsewhere on the board
unnamed: J3.A5 (CC1), R1.2
unnamed: J3.B5 (CC2), R2.2
unnamed: J3.A4 (VBUS), J3.A9 (VBUS), J3.B4 (VBUS), J3.B9 (VBUS), L1.1
unnamed: R7.2, U1.1 (CS), U2.63 (EECS)
unnamed: R5.2, U1.3 (DI), U2.61 (EEDATA)
unnamed: R3.2, R5.1, U1.4 (DO)
unnamed: R4.2, U1.2 (SCLK), U2.62 (EECLK)
unnamed: R13.2, R15.1, R17.1, U2.38 (BDBUS0)
unnamed: R11.2, R16.1, R18.1, U2.39 (BDBUS1)
unnamed: R19.1, U2.40 (BDBUS2)
unnamed: J3.A7 (D-), J3.B7 (D-), U2.7 (DM)
unnamed: J3.A6 (D+), J3.B6 (D+), U2.8 (DP)
unnamed: C3.2, U2.2 (OSCI), Y1.3
unnamed: C5.2, U2.3 (OSCO), Y1.1
unnamed: R8.2, U2.6 (REF)
unnamed: C4.2, C6.2, L3.2, U2.4 (VPHY)
unnamed: C8.2, C9.2, L2.2, U2.9 (VPLL)
unnamed: R6.2, U2.14 (~RESET)

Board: 2 copper layers, 53 parts (0 on the bottom side), 29 nets, no tracks yet.

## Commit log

2025-06-09 Init Kicad projects
2025-06-09 SOM: +DDR IC
2025-06-09 SOM: SO-DIMM connector
2025-06-14 SOM board outline
2025-06-14 BB SOM connector
2025-06-15 SOM: DDR schematics update
2025-06-15 some schematics update
2025-06-15 SOM layout fix
2025-06-23 Baseboard: JTAG
2025-06-28 QSPI, banks IO decoupling
2025-06-29 QSPI connected
2025-06-29 DDR-FPGA connection
2025-06-29 DDR clock termination
2025-06-29 ZQ calibration resistor added
2025-06-30 SOM: Boot mode CFG
2025-07-01 SOM: DDR pull-ups
2025-07-04 PDFs excluded
2025-07-04 gitignore
2025-07-04 DDR Banks Vref
2025-07-08 M.2 connector added
2025-07-09 PCIe M.2 connector changed
2025-07-09 BB: PCIe update
2025-07-10 PCIe AC coupling
2025-07-12 PCIe M.2 pull-ups
2025-07-13 SOM: power supplies
2025-07-13 SOM: power supply update
2025-07-14 SOM: Serdes power
2025-07-21 SOM: components placement
2025-08-10 SOM: layout update
2025-08-13 SOM: QSPI layout update
2025-08-13 SOM: layout update (QSPI+
2025-12-09 SOM stack-up JLC06161H-3313
2025-12-09 Switched to 8-layer stack-up JLC08161H-2116
2025-12-11 some net names added
2025-12-23 SOM: decoupling caps placement
2025-12-23 SOM: more caps moved to their place
2025-12-24 Decopuling placement continued
2025-12-25 DDR clock schematics fixed
2026-01-10 DDR reconnect
2026-01-12 BB schematics: PS
2026-01-13 lic file update
2026-02-08 SOM: DDR PWR UPD

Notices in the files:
README.md:
See the LICENSE file for details.
